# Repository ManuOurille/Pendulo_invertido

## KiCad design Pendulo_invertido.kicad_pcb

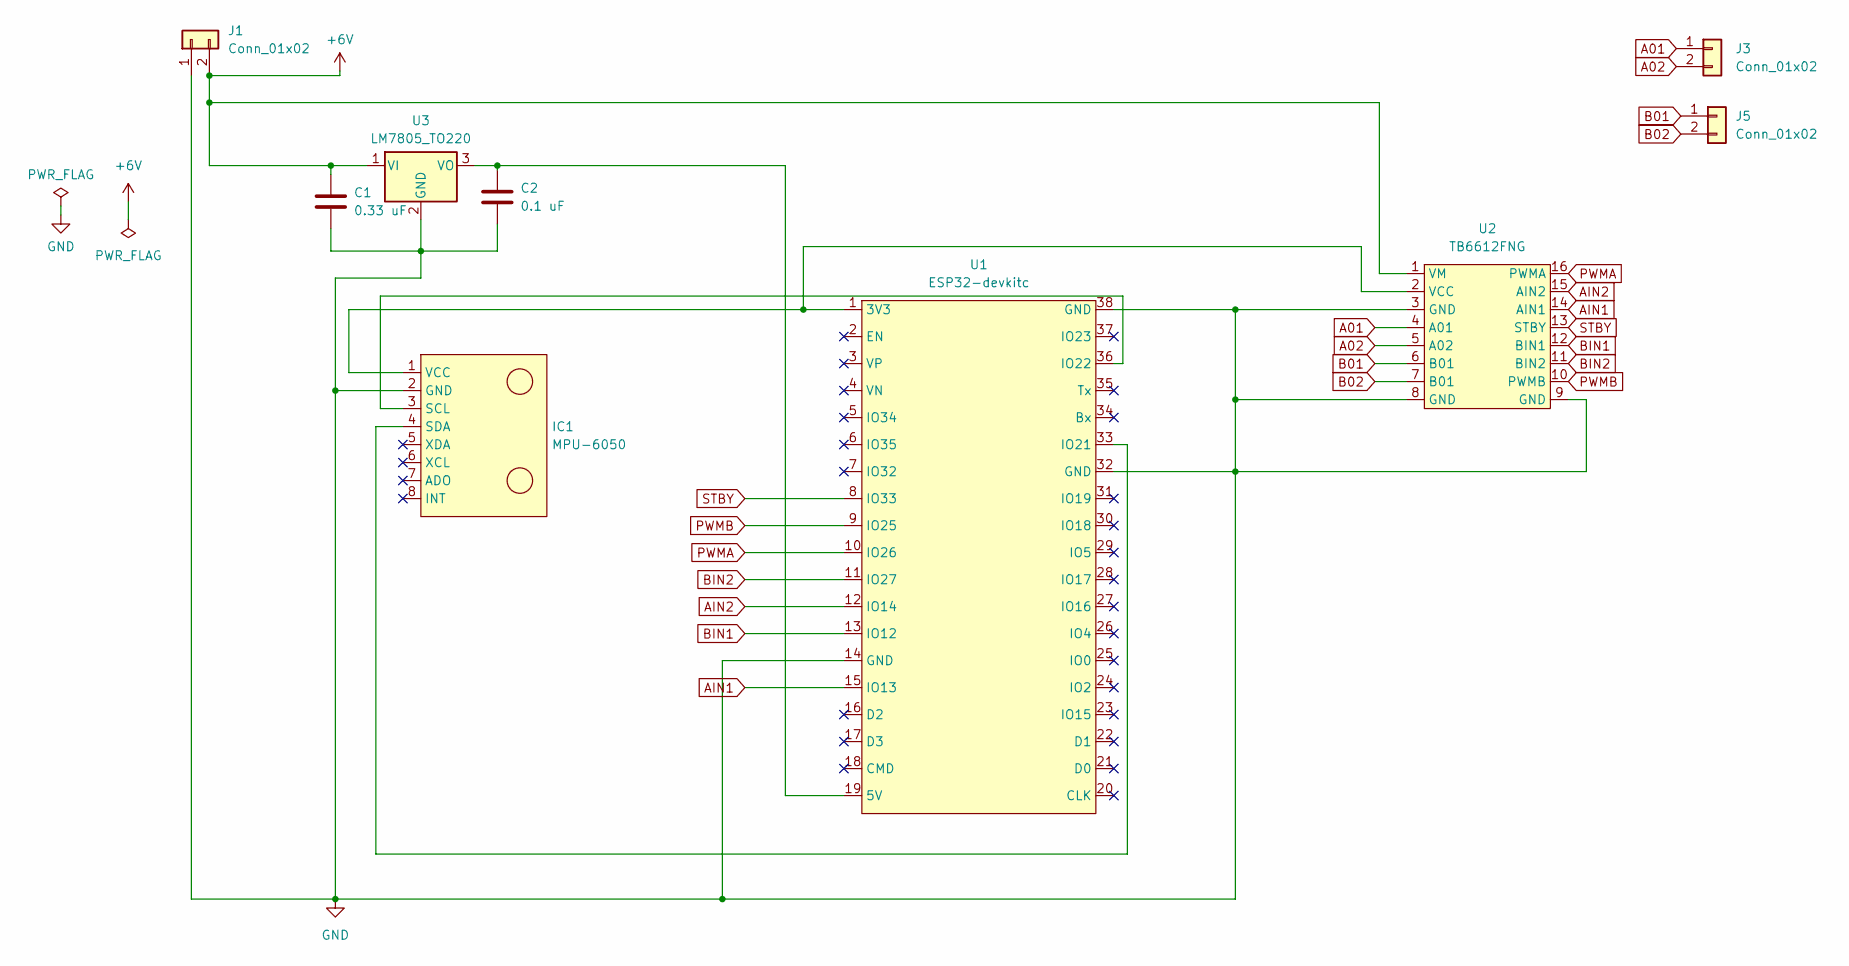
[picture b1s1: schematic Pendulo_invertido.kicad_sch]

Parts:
C1: 0.33 uF; CP_Radial_D5.0mm_P2.00mm
C2: 0.1 uF; CP_Radial_D5.0mm_P2.00mm
IC1: MPU-6050; MPU6050
J1, J3, J5: Conn_01x02; TerminalBlock_Phoenix_MKDS-1,5-2-5.08_1x02_P5.08mm_Horizont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
U1: ESP32-devkitc; ESP32-devkitc-v4
U2: TB6612FNG
U3: LM7805_TO220; TO-220-3_Vertical

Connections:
A01: J3.1, U2.4 (A01)
A02: J3.2, U2.5 (A02)
AIN1: U1.15 (IO13), U2.14 (AIN1)
AIN2: U1.12 (IO14), U2.15 (AIN2)
B01: J5.1, U2.6 (B01)
B02: J5.2, U2.7 (B01)
BIN1: U1.13 (IO12), U2.12 (BIN1)
BIN2: U1.11 (IO27), U2.11 (BIN2)
GND: C1.2, C2.2, IC1.2 (GND), J1.1, U1.14 (GND), U1.32 (GND), U1.38 (GND), U2.3 (GND), U2.8 (GND), U2.9 (GND), U3.2 (GND)
unnamed: IC1.3 (SCL), U1.36 (IO22)
unnamed: IC1.4 (SDA), U1.33 (IO21)
unnamed: IC1.1 (VCC), U1.1 (3V3), U2.2 (VCC)
unnamed: C1.1, J1.2, U2.1 (VM), U3.1 (VI)
unnamed: C2.1, U1.19 (5V), U3.3 (VO)
PWMA: U1.10 (IO26), U2.16 (PWMA)
PWMB: U1.9 (IO25), U2.10 (PWMB)
STBY: U1.8 (IO33), U2.13 (STBY)

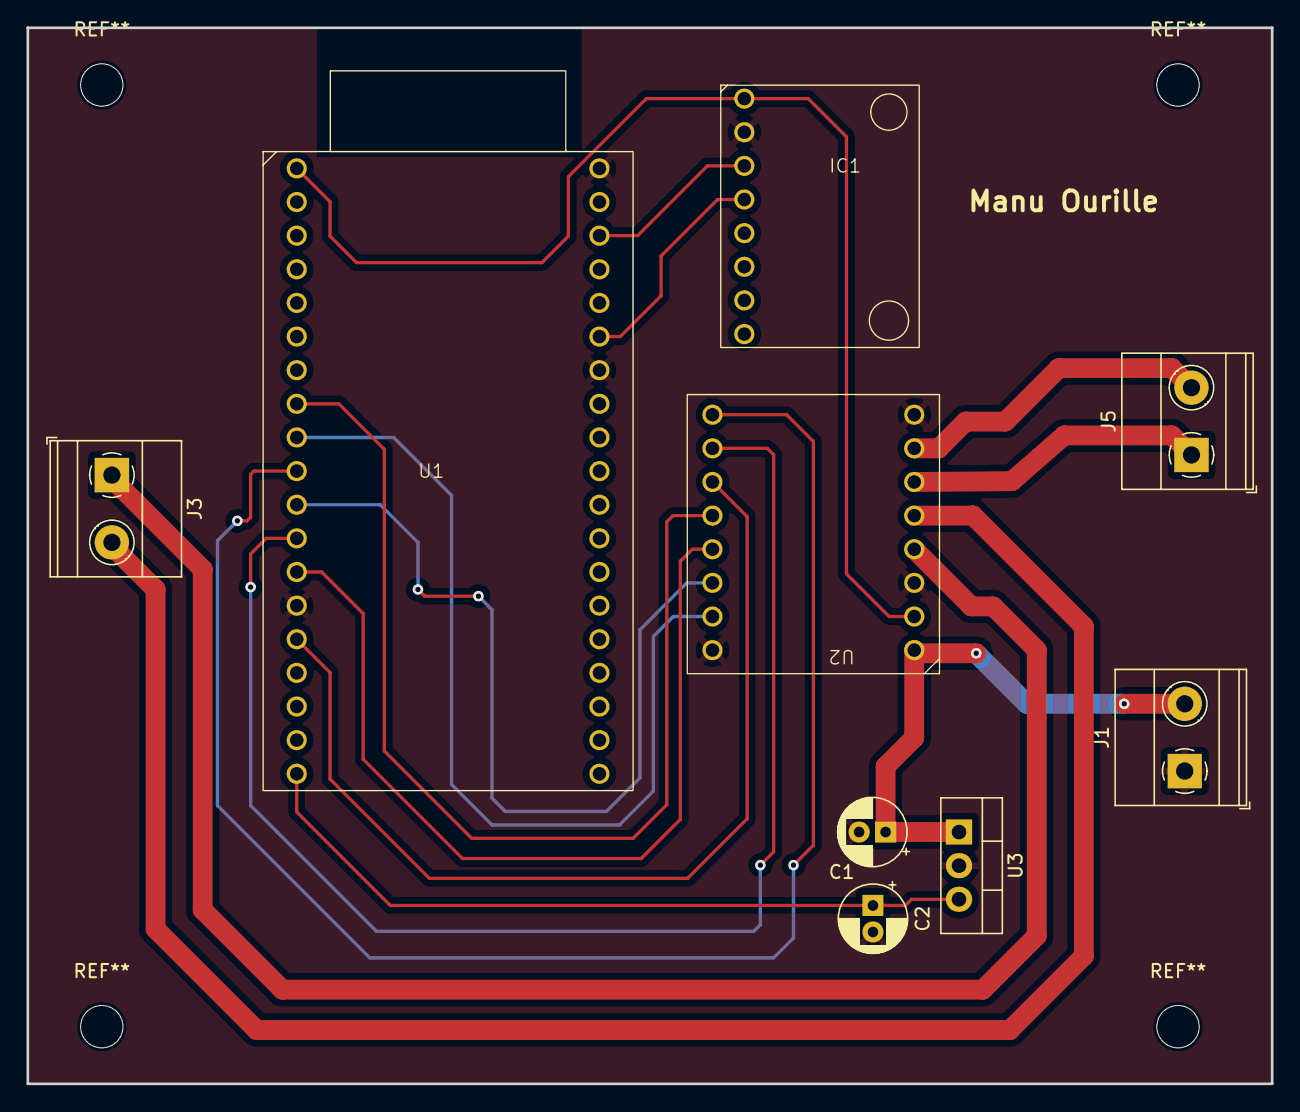
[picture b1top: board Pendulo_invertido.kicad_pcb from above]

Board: 2 copper layers, 94.0 x 79.8 mm, 9 parts (0 on the bottom side), 17 nets.

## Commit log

2024-04-04 Creación primer esquemático
2024-04-06 Creacion huellas esp32 y MPU
2024-04-07 Creación pcb
2024-04-08 Cambios huellas y pcb
2024-04-18 Ultimos cambios y creacion archivos gerber
2024-04-18 Resolucion error de medidas
2024-04-19 Creacion 1º pasos del chasis
2024-04-25 Modificación chasis
2024-05-01 Nuevo chasis
2024-05-06 Modificaciones nuevo chasis
